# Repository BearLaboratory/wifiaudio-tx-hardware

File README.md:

<h1 align="center" style="font-size:50px;font-weight:bold">WiFiAudio</h1>
<p align="center">基于WiFi的语音传输系统</p>
<p align="center">

</p>

整个系统在组织下分为及个仓库，请根据个人的需求参考：
- [语音发射端硬件](https://github.com/BearLaboratory/wifiaudio-tx-hardware)
- [发射端固件](https://github.com/BearLaboratory/wifiaudio-tx-firmware)
- [接收端硬件](https://github.com/BearLaboratory/wifiaudio-rx-hardware)
- [接收端固件](https://github.com/BearLaboratory/wifiaudio-rx-firmware)
- [PC端接收服务](https://github.com/BearLaboratory/wifiaudio-rx-pc)
- [PCM5102A解码验证模块](https://github.com/BearLaboratory/esp32-pcm51202-audio-hardware)

整个系统所使用的到的工具；
- [EDA工具使用开源免费的Kicad](https://www.kicad.org/)
- [固件开发使用简单的Arduino](https://www.arduino.cc/)

# 1. WiFi Audio TX （基于WiFi的无线麦克风发射端硬件）

WiFi Audio项目的目的是DIY一个开源且便宜的无线麦克风，辅助自己在拍摄视频时的收音。项目有几个根本点：
- 软件键全开源，方便大家对软硬件部分进行针对性的修改；
- 整体成本尽量低，为了达到这个目的在硬件设计部分，我舍弃了很多锦上添花的硬件（比如屏幕）；
- 基于WiFi，由于我个人想让麦克风能接入网络，因此抛弃了传统的UHF转而投入了WiFi的怀抱，正巧这两年芯片价格飞涨唯一还算正常的是上来乐鑫的ESP32系列芯片，价格便宜功能强大具有WiFi及蓝牙功能，因此选择它作为我们麦克的核心处理芯片。

麦克风选择我直接抛弃了传统模拟麦克风，虽然价格便宜，但是其外围电路较复杂，电路对声音音质的影响较大，不适合我们DIY。麦克风我测试的有两款一个是inmp441另一款是ics43434，后者是前者的替代品拥有更高的信噪比，我个人十分推荐使用ics43434。当然还有其他麦克风，奈何我自己没有买来测试，如果有小伙伴有自行测试，请将测试结果反馈给我 <mail>dengyi@dengyi.pro</mail>

# 2. 如何自行打板

整个硬件部分已完整打板测试，如果你使用嘉立创下单助手，直接将gebber目录下压缩文件上传即可，我推荐板材厚度选择1,1.6厚度过大，平时自己焊接过程中加热较麻烦。

如果你使用嘉立创smt服务时，上传坐标文件及bom_lc bom清单即可，如果出现错误，你需要手动去调整原件的方向等，确保焊盘准确即可，bom本身无任何问题。

# 2. 如何上传固件

固件部分，请参考其他仓库。对于固件我都是使用arduino进行编写，因此你需要安装arduino IDE，然后克隆固件仓库，然后进行编译上传。

需要特殊说明：因为我想尽量控制设备成本，所以没有板载烧录电路。进行固件的烧写需要使用我之前开发的ESP系列芯片烧录工具，具体的信息请参见这个仓库[ESP系列芯片烧录工具](https://github.com/BearLaboratory/downloader)

# 3. 如何使用

对于如何使用这部分，我推荐大家反复观看我的项目视频。因为我个人精力有限，每次readme文档我都写的比较糙（虽然多次召集负责写readme的小伙伴，但是并未成功）
# 4. 其他

整个项目在GPL协议下开源，禁止商用，商用请联系<mail>dengyi@dengyi.pro</mail>。

组织下所有开源项目均为个人出于兴趣进行开发及维护，并没有任何盈利，所以在维护频率上可能有很大的延迟，如果小伙伴们有兴趣可以发送邮件到<mail>dengyi@dengyi.pro</mail>与我个人联系或参与到开发中。同时非常欢迎对我的视频频道进行点赞或者关注，[B站](https://space.bilibili.com/402729300),[知乎](https://www.zhihu.com/people/deng-yi-92-16/columns),[youtube](https://www.youtube.com/channel/UCXvLKESzLbINYVe9J8rXerQ)

硬件可以个人自行在嘉立创下单打板，如果需要成品请直接在咸鱼搜索用户**BLab大熊实验室**，由于是非职业卖家，快递费由系统自行计算我做不了主还请谅解。

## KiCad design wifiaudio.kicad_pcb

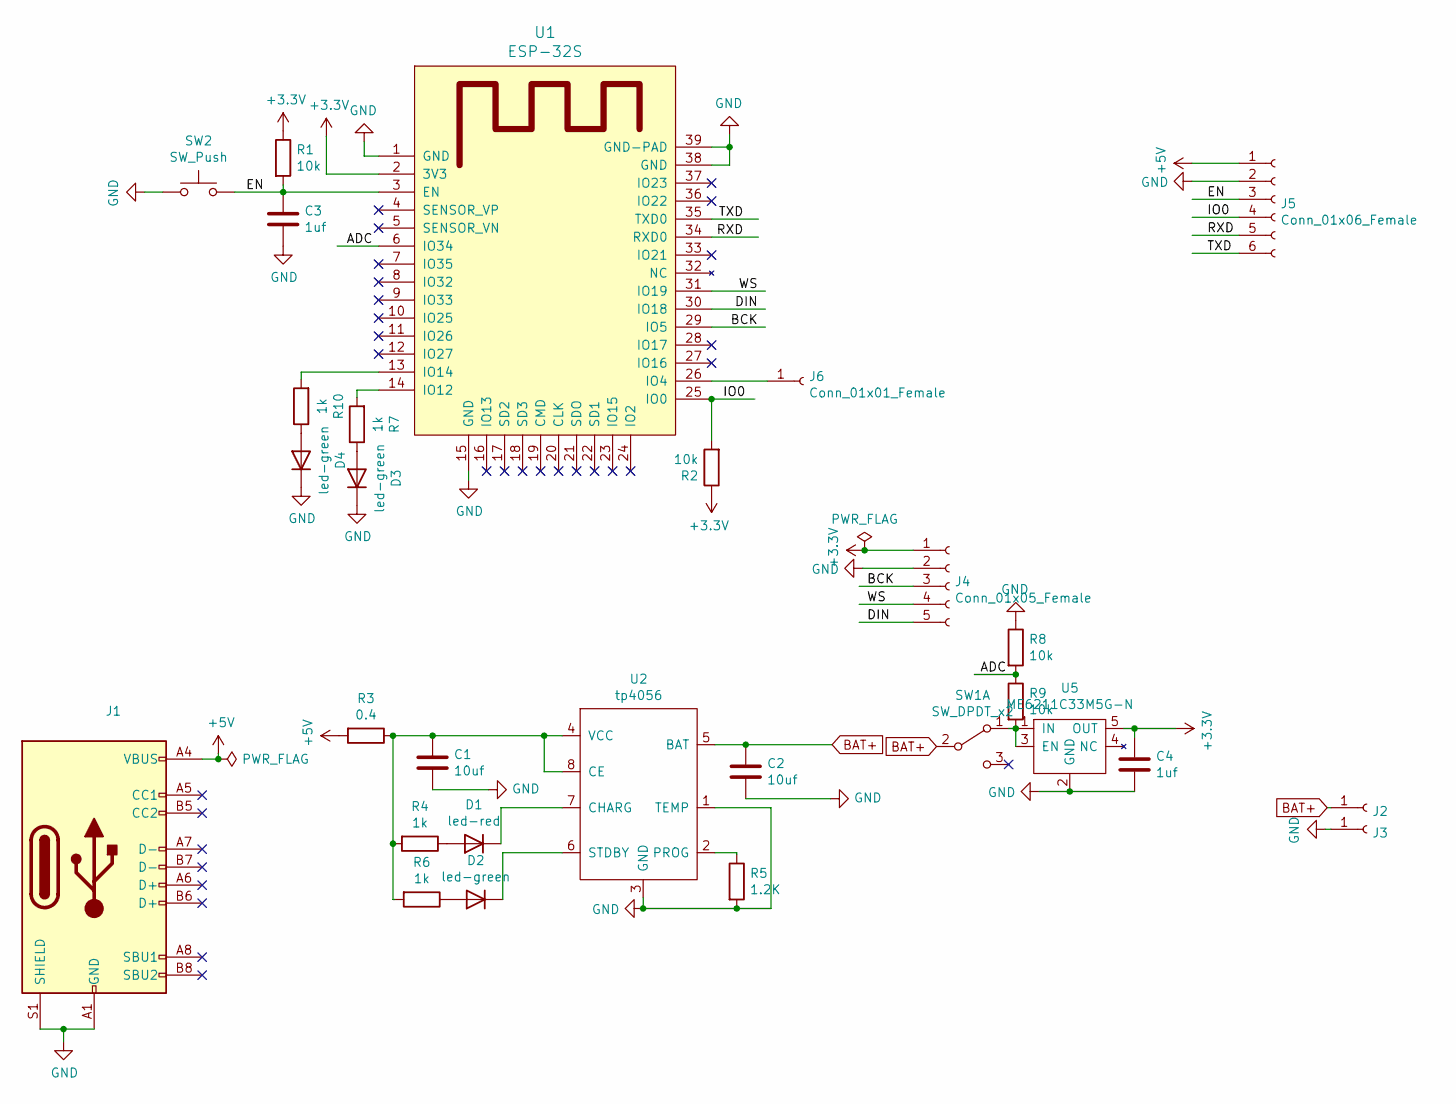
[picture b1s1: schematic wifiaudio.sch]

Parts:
C1, C2: 10uf; C_0603_1608Metric
C3, C4: 1uf; C_0603_1608Metric
D1: led-red; LED_0603_1608Metric
D2, D3, D4: led-green; LED_0603_1608Metric
J1: USB_C_Receptacle_USB2.0; USB_C_Receptacle_HRO_TYPE-C-31-M-12
J2, J3, J6: Conn_01x01_Female; largepoint
J4: Conn_01x05_Female; JST_GH_SM05B-GHS-TB_1x05-1MP_P1.25mm_Horizontal
J5: Conn_01x06_Female; PinHeader_1x06_P2.00mm_Vertical
R1, R2, R8, R9: 10k; R_0603_1608Metric
R3: 0.4; R_0603_1608Metric
R4, R6, R7, R10: 1k; R_0603_1608Metric
R5: 1.2K; R_0603_1608Metric
SW1: SW_DPDT_x2; SW_SPDT_PCM12
SW2: SW_Push; bt-342
U1: ESP-32S; ESP32-WROOM-32
U2: tp4056; SOIC-8-1EP_3.9x4.9mm_P1.27mm_EP2.29x3mm
U5: ME6211C33M5G-N; SOT-23-5

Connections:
+3V3: C4.1, J4.1, R1.1, R2.1, U1.2 (3V3), U5.5 (OUT)
+5V: J1.A4 (VBUS), J1.A9 (VBUS), J1.B4 (VBUS), J1.B9 (VBUS), J5.1, R3.2
/ADC: R8.2, R9.1, U1.6 (IO34)
/BCK: J4.3, U1.29 (IO5)
/DIN: J4.5, U1.30 (IO18)
/EN: C3.1, J5.3, R1.2, SW2.2, U1.3 (EN)
/IO0: J5.4, R2.2, U1.25 (IO0)
/RXD: J5.5, U1.34 (RXD0)
/TXD: J5.6, U1.35 (TXD0)
/WS: J4.4, U1.31 (IO19)
BAT+: C2.1, J2.1, SW1.2 (B), U2.5 (BAT)
GND: C1.2, C2.2, C3.2, C4.2, D3.1 (K), D4.1 (K), J1.A1 (GND), J1.A12 (GND), J1.B1 (GND), J1.B12 (GND), J1.S1 (SHIELD), J3.1, J4.2, J5.2, R5.2, R8.1, SW2.1, U1.1 (GND), U1.15 (GND), U1.38 (GND), U1.39 (GND-PAD), U2.1 (TEMP), U2.3 (GND), U5.2 (GND)
unnamed: C1.1, R3.1, R4.2, R6.2, U2.4 (VCC), U2.8 (CE)
unnamed: D1.1 (K), U2.7 (CHARG)
unnamed: D1.2 (A), R4.1
unnamed: D2.1 (K), U2.6 (STDBY)
unnamed: D2.2 (A), R6.1
unnamed: D3.2 (A), R7.1
unnamed: D4.2 (A), R10.1
unnamed: J6.1, U1.26 (IO4)
unnamed: R5.1, U2.2 (PROG)
unnamed: R7.2, U1.14 (IO12)
unnamed: R9.2, SW1.1 (A), U5.1 (IN), U5.3 (EN)
unnamed: R10.2, U1.13 (IO14)

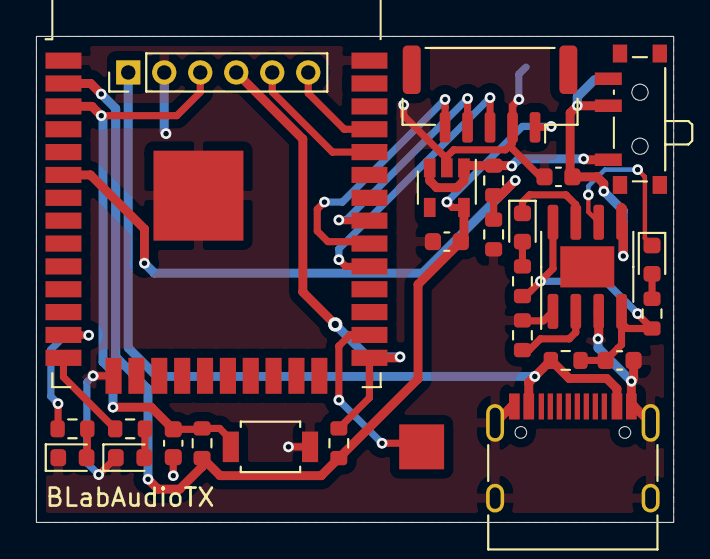
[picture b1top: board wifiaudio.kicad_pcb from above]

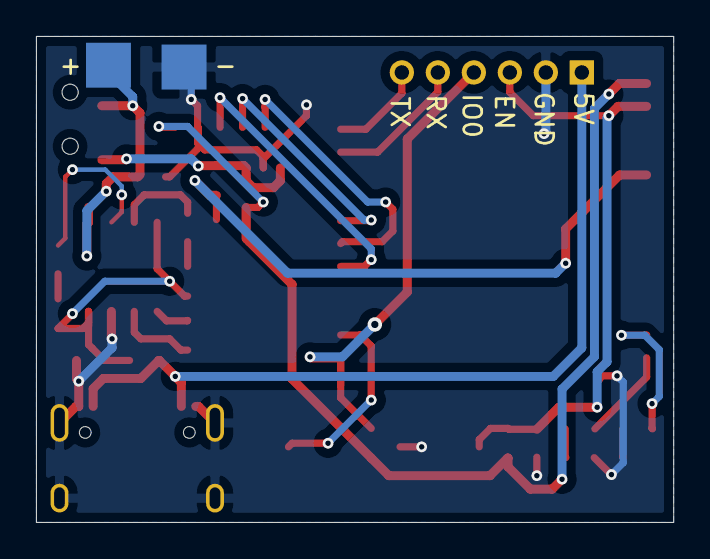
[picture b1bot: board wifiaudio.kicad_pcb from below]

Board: 2 copper layers, 35.4 x 27.0 mm, 29 parts (2 on the bottom side), 24 nets.

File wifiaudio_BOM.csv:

"Comment","Description","Designator","Footprint","LibRef","Pins","Quantity","PartNumber","url",
"10uf","desc","C2,C1,","C_0603_1608Metric","libref","2","2","","",
"1uf","desc","C4,C3,","C_0603_1608Metric","libref","2","2","","",
"led-red","desc","D1,","LED_0603_1608Metric","libref","2","1","","",
"led-green","desc","D4,D3,D2,","LED_0603_1608Metric","libref","2","3","","",
"Conn_01x05_Female","desc","J4,","JST_GH_SM05B-GHS-TB_1x05-1MP_P1.25mm_Horizontal","libref","7","1","","",
"Conn_01x01_Female","desc","J6,","largepoint","libref","1","1","","",
"1k","desc","R10,R7,R6,R4,","R_0603_1608Metric","libref","2","4","","",
"0.4","desc","R3,","R_0603_1608Metric","libref","2","1","","",
"1.2K","desc","R5,","R_0603_1608Metric","libref","2","1","","",
"10k","desc","R8,R2,R1,","R_0603_1608Metric","libref","2","3","","",
"100","desc","R9,","R_0603_1608Metric","libref","2","1","","",
"SW_Push","desc","SW2,","bt-342","libref","2","1","","",
"ESP-32S","desc","U1,","ESP32-WROOM-32","libref","39","1","","",
"tp4056","desc","U2,","SOIC-8-1EP_3.9x4.9mm_P1.27mm_EP2.29x3mm","libref","13","1","","",
"ME6211C33M5G-N","desc","U5,","SOT-23-5","libref","5","1","","",
"Conn_01x01_Female","desc","J3,J2,","largepoint","libref","1","2","","",
"Through Hole Items ",
"USB_C_Receptacle_USB2.0","desc","J1,","USB_C_Receptacle_HRO_TYPE-C-31-M-12","libref","22","1","","",
"Conn_01x06_Female","desc","J5,","PinHeader_1x06_P2.00mm_Vertical","libref","6","1","","",
"SW_DPDT_x2","desc","SW1,","SW_SPDT_PCM12","libref","9","1","","",

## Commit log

2021-10-13 初始化提交
2021-12-02 修改readme
2021-12-02 Create LICENSE

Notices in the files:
README.md:
GPL License
